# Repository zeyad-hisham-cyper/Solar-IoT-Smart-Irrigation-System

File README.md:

# 🌱 Solar-Powered IoT Smart Irrigation System

A distributed, low-power irrigation platform that closes the loop between soil sensors in the
field and a phone in your hand. It is built from **three cooperating subsystems**:

1. **Zone firmware** (ESP32) — battery/solar sensor + valve endpoints that measure soil
   moisture, temperature and water flow, and open/close a solenoid valve on command.
2. **Gateway firmware** (ESP32) — the single Internet-connected node. It runs the irrigation
   decision engine, drives the pump, enforces safety, talks to the zones over **ESP-NOW**, and
   mirrors all state to the cloud over Wi-Fi.
3. **Flutter mobile app** — a real-time dashboard that monitors every zone and lets the user
   switch modes and control valves/pump, talking only to **Firebase Realtime Database**.

> This document is the single engineering reference for the entire project — hardware,
> firmware, cloud schema and mobile app. It is detailed enough for a new engineer to
> understand the architecture, build/flash/run every component, debug issues, and extend the
> system without additional documentation.

---

## Team

Graduation project — **Electronics and Communications Department**, Faculty of Engineering
Sciences and Arts, **Misr International University (MIU)**, Cairo, 2026.

| Member |
|--------|
| Zeyad Hisham |
| Abdelrahman Adel |
| Amr Yasser |
| Ahmed Mohamed Saad |

**Supervisor:** Dr. Ibrahiem Abdalla

---

## Table of Contents

- [1. System Architecture](#1-system-architecture)
- [2. Repository Layout](#2-repository-layout)
- [3. Hardware Reference](#3-hardware-reference)
  - [3.1 Boards & Power](#31-boards--power)
  - [3.2 Complete GPIO Mapping](#32-complete-gpio-mapping)
  - [3.3 Bill of Materials (minimum)](#33-bill-of-materials-minimum)
  - [3.4 PCB Design (KiCad)](#34-pcb-design-kicad)
- [4. ESP-NOW Network](#4-esp-now-network)
- [5. Firmware Design](#5-firmware-design)
  - [5.1 Software Architecture](#51-software-architecture)
  - [5.2 Gateway (Control) Node](#52-gateway-control-node)
  - [5.3 Zone Node](#53-zone-node)
  - [5.4 Communication Flow](#54-communication-flow)
  - [5.5 Packet Structures](#55-packet-structures)
  - [5.6 State Machines](#56-state-machines)
  - [5.7 Sensor Processing](#57-sensor-processing)
  - [5.8 Irrigation Decision Logic](#58-irrigation-decision-logic)
  - [5.9 Power Management](#59-power-management)
  - [5.10 Status LEDs & Buzzer](#510-status-leds--buzzer)
- [6. Cloud — Firebase](#6-cloud--firebase)
  - [6.1 Architecture](#61-architecture)
  - [6.2 Database Schema](#62-database-schema)
- [7. Mobile App (Flutter)](#7-mobile-app-flutter)
  - [7.1 Architecture](#71-architecture)
  - [7.2 Project Structure](#72-project-structure)
  - [7.3 Command & Control Mapping](#73-command--control-mapping)
- [8. Build, Flash & Run](#8-build-flash--run)
- [9. Configuration Guide](#9-configuration-guide)
- [10. Testing Procedures](#10-testing-procedures)
- [11. Troubleshooting](#11-troubleshooting)
- [12. Error Handling & Safety](#12-error-handling--safety)
- [13. Future Improvements](#13-future-improvements)
- [14. License](#14-license)

---

## 1. System Architecture

The system is organised into four layers. Zone nodes never touch the Internet; the gateway is
the only cloud-connected device; the app talks only to Firebase.

```mermaid
flowchart TD
    subgraph ZL["Zone Layer (battery / solar)"]
        Z1["Zone Node 1<br/>soil • temp • flow • valve"]
        Z2["Zone Node N<br/>soil • temp • flow • valve"]
    end
    subgraph CL["Control Layer (gateway)"]
        G["Gateway / Control Node<br/>irrigation engine • pump • water level"]
    end
    subgraph CLD["Cloud Layer"]
        FB[("Firebase RTDB")]
        WAPI(("OpenWeather API"))
    end
    subgraph AL["Application Layer"]
        APP["Flutter Dashboard"]
    end

    Z1 <-- "ESP-NOW (2.4 GHz)" --> G
    Z2 <-- "ESP-NOW (2.4 GHz)" --> G
    G <-- "Wi-Fi / HTTPS" --> FB
    G -- "HTTPS GET" --> WAPI
    APP <-- "RTDB SDK" --> FB
```

| Direction | Path | Protocol |
|-----------|------|----------|
| Zone → Gateway | soil moisture, temperature, flow, needs-water | ESP-NOW |
| Gateway → Zone | valve open/close commands | ESP-NOW (reliable, ACK'd) |
| Gateway → Firebase | gateway state, zone telemetry, weather | HTTPS REST (PUT) |
| Firebase → Gateway | mode, per-zone config, manual commands | HTTPS REST (GET poll, 2 s) |
| Firebase ↔ App | all reads + command writes | Firebase SDK (real-time streams) |

**The Flutter app never communicates with the ESP32 boards directly** — all interaction is
mediated through Firebase Realtime Database.

### Design objectives

| Objective | How it is met |
|-----------|---------------|
| Reliable irrigation | Closed-loop moisture control + duration limits + weather awareness |
| Safety | Pump active-LOW safe-OFF, valve 10-min auto-close, dry-run protection, uncalibrated-reading rejection, ACK'd valve commands |
| Maintainability | Pure-C component-based HAL/Services separation; layered Flutter app; documented APIs |
| Scalability | Up to 8 zones per gateway (NVS registry); extensible, versioned ESP-NOW protocol |
| Low power | Soil-sensor power-gating, event-driven tasks, no busy-wait polling |
| Observability | Per-board status LEDs + buzzer driven by an explicit lifecycle state machine |

---

## 2. Repository Layout

```
.
├── README.md                      # ← this document (the single project reference)
├── docs/
│   └── architecture.png           # system architecture diagram
│
├── PCBs/                          # KiCad hardware design (gateway + zone boards)
│   ├── Control Schematic.png      # rendered gateway schematic
│   ├── control 3D.png             # gateway board 3D render
│   ├── Zone Schematic.png         # rendered zone schematic
│   ├── Zone 3D.png                # zone board 3D render
│   ├── control/                   # GATEWAY KiCad project (.kicad_sch/_pcb/_pro) + BoM csv
│   ├── Zone/                      # ZONE KiCad project + gerbers/ + final_gerber/ + lib/
│   ├── light/                     # SMART LIGHTING relay board KiCad project + BoM csv
│   ├── gerbers/                   # fabrication outputs (control, zones, light)
│   ├── fritzing/                  # early breadboard prototypes (.fzz) + wiring images
│   └── BOM/                       # proof-of-concept bill of materials (.xlsx)
│
├── firebase/                      # Firebase RTDB data model (db.md), seed data, sample export
│
├── firmware/                      # ESP-IDF firmware (two apps + shared components)
│   ├── db.json                    # authoritative Firebase RTDB schema export
│   ├── common/                    # shared components (EXTRA_COMPONENT_DIRS)
│   │   ├── esp_now/               # protocol + reliable send
│   │   ├── led_driver/            # non-blocking LED (blink/pulse) via esp_timer
│   │   ├── buzzer_driver/         # active/passive buzzer pattern player
│   │   └── state_machine/         # tiny reusable FSM engine
│   ├── control/                   # GATEWAY app
│   │   └── main/
│   │       ├── HAL/{Pump,WaterLevel,WiFi,DcMotor,FlowMeter}/
│   │       ├── Services/{FirebaseAuth,FirebaseDB,FirebaseSync,Weather,IrrigationEngine}/
│   │       └── include/{app_config.h, firebase_config.h}
│   └── zone/                      # ZONE app
│       └── main/
│           ├── HAL/{soil_moisture,ds18b20,valve,FlowMeter}/
│           └── include/app_config.h
│
└── app/                           # Flutter mobile dashboard
    ├── lib/
    │   ├── core/                  # constants, theme, utils
    │   ├── data/                  # repositories + Firebase services
    │   ├── models/                # data models (gateway, zone, command, weather)
    │   ├── providers/             # Riverpod providers (streams + commands)
    │   ├── presentation/          # screens + widgets
    │   └── routes/                # GoRouter configuration
    ├── android/ ios/ web/ windows/ macos/ linux/
    └── pubspec.yaml
```

Design rules (firmware): hardware access lives in `HAL/`; business logic in `Services/`;
cross-cutting board-agnostic drivers live in `common/`. The irrigation engine never touches
GPIO directly — it calls the pump driver and sends ESP-NOW commands.

---

## 3. Hardware Reference

### 3.1 Boards & Power

Two ESP32-WROOM-32 board types share a solar power architecture
(solar → MPPT → battery → buck/LDO rails).

```mermaid
flowchart LR
    SOLAR["Solar Panel 12-24V"] --> MPPT["MPPT Charger"]
    MPPT --> BAT["Battery 12V"]
    BAT --> VBAT["VBAT rail<br/>pump, valves"]
    BAT --> BUCK["Buck 5V"] --> V5["5V rail<br/>flow meter, driver logic"]
    BUCK --> LDO["LDO 3.3V"] --> V3["3.3V rail<br/>ESP32, sensors"]
```

| Board | Qty | Actuators | Sensors | Indicators |
|-------|-----|-----------|---------|------------|
| **Gateway / Control** | 1 | Pump (MOSFET, active-LOW) | Water level (ADC) | Green/Yellow/Red LED + buzzer |
| **Zone** | N (≤8) | Solenoid valve (MOSFET) | Soil moisture (ADC, power-gated), DS18B20 temp, YFS-401 flow | Green/Yellow/Red LED + buzzer |

| Rail | Voltage | Consumers |
|------|---------|-----------|
| VBAT | 12–24 V | Water pump motor, solenoid valves |
| 5 V | 5 V | Flow meter, motor-driver logic |
| 3.3 V | 3.3 V | ESP32, DS18B20, soil moisture sensor, all GPIO logic |

**Power budget (typical):** ESP32 Wi-Fi 80–160 mA · ESP32 ESP-NOW 50–100 mA · soil sensor
10–20 mA (power-gated) · DS18B20 <1.5 mA · YFS-401 5–10 mA · solenoid coil 200–400 mA ·
pump 1–5 A (load dependent).

**Key PCB notes:** keep a 10 mm clear zone under the ESP32 PCB antenna; place a 4.7 kΩ
DS18B20 pull-up near its connector; route ADC traces away from switching/motor lines; add a
flyback diode across the solenoid coil and freewheeling diodes on the motor driver outputs;
100 nF close to each VCC pin + 10 µF bulk per rail.

### 3.2 Complete GPIO Mapping

**Gateway / Control Board**

| Function | GPIO | Notes |
|----------|------|-------|
| Pump switch | **GPIO25** | MOSFET, **active-LOW**: LOW = ON, HIGH = OFF (safe). Pull-up holds OFF at boot |
| Water level sensor | GPIO34 | ADC1_CH6, input-only |
| Buzzer | GPIO32 | LEDC tone (passive) |
| Green LED | GPIO26 | Healthy / idle |
| Yellow LED | GPIO27 | Busy / pump running |
| Red LED | GPIO14 | Fault / dry tank |

**Zone Board**

| Function | GPIO | Notes |
|----------|------|-------|
| Soil moisture ADC | GPIO35 | ADC1_CH7, input-only, power-gated |
| Soil sensor VCC control | GPIO25 | HIGH = sensor powered |
| Calibration button | GPIO0 | Boot button, active-LOW, ISR |
| DS18B20 data | GPIO18 | 1-Wire, 4.7 kΩ pull-up |
| Flow sensor (YFS-401) | GPIO19 | Rising-edge ISR |
| Valve | GPIO23 | MOSFET, HIGH = open |
| Red LED | GPIO32 | Fault / not paired |
| Yellow LED | GPIO26 | Valve open / calibrating |
| Green LED | GPIO27 | Paired / idle |
| Buzzer | GPIO33 | LEDC tone (passive) |

All pin assignments are centralised in each app's `main/include/app_config.h`.

### 3.3 Bill of Materials (minimum)

**Zone node:** ESP32-WROOM-32 · AMS1117-3.3 LDO · MP1584/LM2596 buck · IRLZ44N N-MOSFET
(valve) · 1N4007 flyback · 4.7 kΩ (DS18B20 pull-up) · 330 Ω (MOSFET gate) · 10 kΩ (flow
pull-up) · capacitive soil sensor · DS18B20 · YFS-401 flow meter · 12 V solenoid valve ·
tactile switches (calibration + reset) · screw terminals.

**Gateway node:** ESP32-WROOM-32 · motor driver (MOSFET/H-bridge) · AMS1117-3.3 LDO ·
Schottky freewheeling diodes · bypass/bulk caps · reset switch · screw terminals (pump,
water-level sensor, power).

### 3.4 PCB Design (KiCad)

The gateway and zone boards are custom two-layer PCBs designed in **KiCad 8**; a third board
drives the campus **smart-lighting** relays. The full design sources live in
[`PCBs/`](PCBs/) — schematics, layouts, fabrication gerbers and the bill-of-materials CSVs are
all version-controlled, so each board can be reviewed, edited and re-fabricated from this repo.

| Board | KiCad project | Fabrication outputs | BoM |
|-------|---------------|---------------------|-----|
| **Gateway / Control** | [`PCBs/control/control.kicad_pro`](PCBs/control/control.kicad_pro) | — | [`control.csv`](PCBs/control/control.csv) |
| **Zone** | [`PCBs/Zone/Zone.kicad_pro`](PCBs/Zone/Zone.kicad_pro) | [`gerber/`](PCBs/Zone/gerber/), [`final_gerber/`](PCBs/Zone/final_gerber/) | [`Zone.csv`](PCBs/Zone/Zone.csv) |
| **Smart Lighting** | [`PCBs/light/light.kicad_pro`](PCBs/light/light.kicad_pro) | [`gerbers/light/`](PCBs/gerbers/light/) | [`light.csv`](PCBs/light/light.csv) |

Fabrication-ready gerber + drill sets for every board are also collected in
[`PCBs/gerbers/`](PCBs/gerbers/) (`control/`, `zones/`, `Zones Single/`, `light/`). Early
breadboard prototypes made in **Fritzing** (`.fzz` + wiring images) are in
[`PCBs/fritzing/`](PCBs/fritzing/), and the proof-of-concept bill of materials is in
[`PCBs/BOM/`](PCBs/BOM/).

#### Smart Lighting board

A 12 V relay controller for campus lighting, built around a **NodeMCU (ESP-12E)**:

| Block | Parts |
|-------|-------|
| MCU | NodeMCU 1.0 (ESP-12E) on two 15-pin headers |
| Power | 12 V input → **LM2596** buck module → 5 V / 3.3 V rails, bulk + decoupling capacitors |
| Load switching | 4 × **SRD-12VDC-SL-C** relays, each isolated by a **PC817** optocoupler and driven by a **2N2222** transistor with a **1N4007** flyback diode (hierarchical sheet [`realy_module.kicad_sch`](PCBs/light/realy_module.kicad_sch)) |
| Indicators | 2 × **74HC595** shift registers driving 16 status LEDs |
| I/O | 5 × 2-pin screw terminals for supply and lamp outputs, TL2285EE push-button |

The zone project bundles its custom symbol/footprint library and the third-party YAAJ **LM2596**
buck-converter footprint under [`PCBs/Zone/lib/`](PCBs/Zone/lib/). Open a board with
`File → Open Project` in KiCad and use the 3D viewer to inspect placement and clearances.

| Gateway schematic | Gateway 3D | Zone schematic | Zone 3D |
|:-----------------:|:----------:|:--------------:|:-------:|
|  |  |  |  |

> **Repo hygiene:** KiCad auto-backups (`*-backups/`), autosaves, the `fp-info-cache`, per-user
> `*.kicad_prl` state and the heavy vendor 3D models (`*.step`/`*.wrl`) are git-ignored. The
> LM2596 STEP/WRL previews are downloadable from the vendor if you want the full 3D render.

---

## 4. ESP-NOW Network

A star topology: one gateway, up to 8 zones. No router is required for the local link; the
gateway additionally joins the home Wi-Fi AP for cloud access.

```mermaid
flowchart TD
    G(("Gateway<br/>sender_id = 0"))
    Z1["Zone 1"]
    Z2["Zone 2"]
    Zn["Zone N (<=8)"]
    G <-->|"DISCOVERY / ASSIGN / COMMAND"| Z1
    G <-->|"ZONE_DATA"| Z1
    G <--> Z2
    G <--> Zn
```

- **Protocol version 4** (`ESP_NOW_PROTOCOL_VERSION`). Every packet starts with a 3-byte
  header `{version, msg_type, sender_id}`; mismatched versions are dropped.
- **Channel:** the gateway tracks its Wi-Fi AP channel and pins ESP-NOW to it. Zones scan
  channels 1–13 during discovery, then persist the pairing.
- **MAC obfuscation:** zone MACs are XOR-obfuscated (key `0xA5`) inside discovery payloads — a
  lightweight anti-sniffing deterrent, not encryption.
- **Reliable delivery:** safety-critical valve commands use `EspNow_SendReliable()`, which
  waits for the link-layer ACK and retransmits (up to 4 attempts). Telemetry is best-effort.
- **Recovery:** a zone that sees 5 consecutive send failures wipes its pairing and re-discovers.

---

## 5. Firmware Design

ESP-IDF **v5.x**, component-based, **two apps + shared components**, pure C throughout.
Shared components are discovered through `EXTRA_COMPONENT_DIRS=../common` in each project's
top-level `CMakeLists.txt`.

### 5.1 Software Architecture

```
firmware/
├── common/        esp_now · led_driver · buzzer_driver · state_machine   (shared)
├── control/       GATEWAY  →  HAL/ + Services/ + include/
└── zone/          ZONE     →  HAL/ + include/
```

### 5.2 Gateway (Control) Node

```mermaid
flowchart TD
    RX["ESP-NOW RX cb"] -->|ZONE_DATA| ENG["Irrigation Engine<br/>(mutex-protected)"]
    RX -->|DISCOVERY_RESP| REG["Zone Registry (NVS)"]
    WL["Water-level task (5 s)"] --> ENG
    WEA["Weather task (3 h)"] --> ENG
    POLL["Firebase poll (2 s)"] --> ENG
    CYC["Irrigation cycle (1 s)"] --> ENG
    ENG -->|valve cmd, reliable| TX["ESP-NOW TX"]
    ENG --> PUMP["Pump (GPIO25, active-LOW)"]
    ENG --> UP["Firebase upload (2 s)"]
    ENG --> FSM["Lifecycle FSM -> LEDs/Buzzer"]
```

Responsibilities: zone discovery/registration (NVS), telemetry ingestion, the irrigation
decision engine, pump control with dry-run protection, weather fetch, and Firebase sync.

### 5.3 Zone Node

```mermaid
flowchart TD
    SL["Sensor loop (3 s)<br/>soil • temp • flow"] --> SNAP["Shared snapshot<br/>(spinlock)"]
    SNAP --> TX["TX task (2 s)<br/>ZONE_DATA"]
    RX["ESP-NOW RX cb"] -->|COMMAND| VALVE["Valve (GPIO23)"]
    RX -->|DISCOVERY/ASSIGN| PAIR["Pairing (NVS)"]
    BTN["Calibration button ISR"] --> CAL["Calibration task"]
    SAFE["Valve safety task (5 s)"] --> VALVE
    FSM["Lifecycle FSM -> LEDs/Buzzer"]
```

Responsibilities: sensor acquisition, pairing/discovery, valve actuation on gateway command,
interrupt-driven calibration, and the valve safety timeout (10-min auto-close).

### 5.4 Communication Flow

**Discovery & assignment**

```mermaid
sequenceDiagram
    participant G as Gateway
    participant Z as Zone
    G-->>Z: DISCOVERY_REQ (broadcast, periodic)
    Z-->>G: DISCOVERY_RESP (obfuscated MAC)
    G->>G: find/register zone in NVS -> zone_id
    G-->>Z: ZONE_ASSIGN (zone_id)  [unicast]
    Z->>Z: persist {zone_id, gateway MAC} in NVS
```

**Steady-state telemetry & control**

```mermaid
sequenceDiagram
    participant Z as Zone
    participant G as Gateway
    loop every 2 s
        Z-->>G: ZONE_DATA (sm, temp, flow, vol, needs_water)
    end
    Note over G: engine decides per cycle (1 s)
    G-->>Z: COMMAND open/close (reliable, ACK + retry)
    Z->>Z: drive valve, FSM -> IRRIGATING / PAIRED_IDLE
```

### 5.5 Packet Structures

All structs are `__attribute__((packed))` and prefixed with the common header.

```c
typedef struct __attribute__((packed)) {
    uint8_t version;     // = ESP_NOW_PROTOCOL_VERSION (4)
    uint8_t msg_type;    // EspNow_MsgType_t
    uint8_t sender_id;   // zone id, or 0 for the gateway
} EspNow_MessageHeader_t;
```

| Type | ID | Direction | Payload (beyond header) |
|------|----|-----------|-------------------------|
| `ZONE_DATA` | 1 | Zone → GW | `moisture%` (0xFF = invalid), `temp_x10` (-999 = invalid), `needs_water`, `total_volume_ml`, `flow_rate_x100` |
| `COMMAND` | 2 | GW → Zone | `target_zone_id`, `open_valve` |
| `DISCOVERY_REQ` | 3 | GW → bcast | — |
| `DISCOVERY_RESP` | 4 | Zone → GW | `obfuscated_mac[6]` |
| `ZONE_ASSIGN` | 5 | GW → Zone | `assigned_zone_id` |

Sentinels: `ESP_NOW_MOISTURE_INVALID = 0xFF`, `ESP_NOW_TEMP_INVALID = -999`. The gateway treats
an invalid moisture as out-of-range and will never irrigate on it.

### 5.6 State Machines

Both apps drive an explicit lifecycle FSM (`common/state_machine`) whose transitions are logged
and mapped to the status indicators.

**Gateway**

```mermaid
stateDiagram-v2
    [*] --> BOOT
    BOOT --> INIT
    INIT --> INIT_ESPNOW
    INIT_ESPNOW --> CONNECT_WIFI
    CONNECT_WIFI --> RUNNING
    RUNNING --> IRRIGATING: pump on
    IRRIGATING --> RUNNING: pump off
    RUNNING --> TANK_DRY: level < threshold
    TANK_DRY --> RUNNING: refilled
    INIT_ESPNOW --> ERROR: ESP-NOW init fail
```

**Zone**

```mermaid
stateDiagram-v2
    [*] --> BOOT
    BOOT --> INIT
    INIT --> DISCOVERY
    DISCOVERY --> PAIRED_IDLE: ZONE_ASSIGN
    PAIRED_IDLE --> IRRIGATING: COMMAND open
    IRRIGATING --> PAIRED_IDLE: COMMAND close / safety timeout
    PAIRED_IDLE --> CALIBRATING: button
    CALIBRATING --> PAIRED_IDLE
    DISCOVERY --> ERROR: pairing failed -> restart
```

### 5.7 Sensor Processing

| Sensor | Processing | Failure handling |
|--------|-----------|------------------|
| **Soil moisture** | Power-gate ON → 100 ms settle → 64-sample average → map with NVS dry/wet calibration → 0–100 % → power OFF | **Uncalibrated/invalid ⇒ `valid=false`**; the zone transmits `0xFF` so the gateway never irrigates on it |
| **DS18B20** | 12-bit conversion, up to 3 retries; ~750 ms conv time | Invalid ⇒ `temp_x10 = -999`; does not block irrigation |
| **YFS-401 flow** | Rising-edge ISR increments a cumulative counter; rate from Δpulses/Δt; volume recomputed from the cumulative count in 64-bit (no truncation loss); spinlock guards counters across cores | Zero on first call; safe against div-by-zero |
| **Water level** | 16–32 sample average mapped between calibrated empty/full raw values; either polarity | Read failure ⇒ keep last value; `valid=false` disables dry-run gating (fails open) |

### 5.8 Irrigation Decision Logic

The engine runs every second under a mutex. Order of operations each cycle:

```mermaid
flowchart TD
    A["heartbeat check<br/>(mark stale zones inactive)"] --> B["duration check<br/>(close expired valves)"]
    B --> C{"water available?"}
    C -- no --> D["stop all + pump OFF<br/>state = TANK_DRY"]
    C -- yes --> E{mode}
    E -- AUTO --> F["per zone: if rain -> stop;<br/>else sm<th -> open (until sm>=th);<br/>sm>=th -> close"]
    E -- MANUAL --> G["pump=false -> stop all;<br/>per zone: v=true -> open (with dur);<br/>v=false -> close"]
    F --> H["pump OFF if no active zone"]
    G --> H
```

**Safety invariants**
- Pump ON requires water available **and** at least one eligible zone below threshold.
- A zone is *eligible* only if its data is valid, fresh (< 10 s) and in range — an invalid
  (`0xFF`) moisture is rejected at ingestion and can never start irrigation.
- The pump turns ON before any valve opens (`PUMP_SETTLE_DELAY_MS`), and OFF once no valve is open.
- Manual mode still enforces the threshold and dry-run safety.

### 5.9 Power Management

This deployment uses an **always-on** model because the gateway commands zone valves in real
time and auto mode is closed-loop on the live moisture stream. Within that model:

- **Soil sensor is power-gated** — energised only for the ~100 ms measurement window.
- **No busy-wait polling.** Calibration is interrupt-driven (button ISR); flow counting is
  ISR-driven; tasks block on timers/notifications/event-groups rather than spinning.
- **Water level** is sampled at a slow cadence (5 s).
- **Outputs default to safe/off** at boot and are disabled before the system goes idle.

> **Deep sleep was deliberately not enabled.** A sleeping zone cannot receive live valve
> `COMMAND` packets, and auto mode holds a valve open until the *streamed* moisture crosses the
> threshold. Adopting deep sleep requires a **zone-autonomous duty-cycle** protocol redesign
> (wake → measure → report → receive a fixed duration → run the valve locally → sleep), listed
> under [Future Improvements](#13-future-improvements).

### 5.10 Status LEDs & Buzzer

**Gateway**

| State | Green | Yellow | Red | Buzzer |
|-------|:-----:|:------:|:---:|--------|
| BOOT / INIT | off | fast blink | off | — |
| CONNECT_WIFI | off | slow blink | off | — |
| RUNNING (idle) | **on** | off | off | success chirp on entry |
| IRRIGATING | off | **on** | off | — |
| TANK_DRY | off | off | blink | warning |
| ERROR | off | off | **on** | error pattern |

**Zone**

| State | Green | Yellow | Red | Buzzer |
|-------|:-----:|:------:|:---:|--------|
| BOOT / INIT | off | fast blink | off | — |
| DISCOVERY (unpaired) | off | off | slow blink | — |
| PAIRED_IDLE | **on** | off | off | success on pairing |
| IRRIGATING (valve open) | off | **on** | off | — |
| CALIBRATING | off | fast blink | off | success/error on finish |
| ERROR | off | off | **on** | error pattern |

Buzzer patterns: `success` (rising two-tone), `warning` (two beeps), `error` (three low beeps),
`alarm` (continuous until stopped).

---

## 6. Cloud — Firebase

### 6.1 Architecture

```mermaid
sequenceDiagram
    participant G as Gateway
    participant ID as Identity Toolkit
    participant DB as RTDB
    G->>ID: signInWithPassword(email, pw)
    ID-->>G: idToken
    loop every 2 s
        G->>DB: PUT gateways/g1, zones/zX  (?auth=idToken)
        G->>DB: GET gateways/g1.mode, zones/zX.{th,dur}, commands/g1
    end
    Note over G,DB: On HTTP 401 -> re-auth -> retry once
```

- **Auth:** email/password → `idToken`, attached as `?auth=` to every REST call. A `401`
  triggers a transparent re-login and one retry.
- **Upload (2 s, or immediate on critical change):** `gateways/g1` and `zones/z1..z2`.
- **Poll (2 s):** gateway `mode`, per-zone `th`/`dur`, and `commands/g1`.
- **Resilience:** read failures preserve the last known config; uploads never block the engine.
  Timestamps are only published once SNTP has synced (no bogus `-1`).

### 6.2 Database Schema

Authoritative export: [`firmware/db.json`](firmware/db.json). Firmware field names match exactly.

```
gateways/g1/
  ├─ mode        (string)  "auto" | "manual"        [cloud -> device]
  ├─ pump        (bool)    pump running              [device -> cloud]
  ├─ waterLevel  (number)  reservoir 0-100 %         [device -> cloud]
  └─ lastSeen    (number)  epoch ms                  [device -> cloud]

zones/z{1,2}/
  ├─ g    (string)  parent gateway id "g1"
  ├─ sm   (number)  soil moisture 0-100 %
  ├─ t    (number)  temperature C
  ├─ f    (number)  flow rate L/min
  ├─ v    (bool)    valve open
  ├─ lu   (number)  last update epoch ms
  ├─ th   (number)  moisture threshold %  [cloud -> device]
  ├─ dur  (number)  irrigation duration s [cloud -> device]
  └─ history/{id}   time-series readings (temp, moisture, flow, water used, valve, ts)

commands/g1/
  ├─ pump (bool)            master pump enable (false = stop all)  [cloud -> device]
  ├─ ts   (number)          command timestamp
  └─ z/z{1,2}/{ v(bool), d(number seconds), commandId, status }    [cloud -> device]

commandAcks/g1/z{1,2}/  { commandId, status, executedAt, message } [device -> cloud]

weather/  { temperature, humidity, condition, timestamp }          [device -> cloud]
```

**Schema notes**
- `f` carries the instantaneous flow rate in L/min (consistent with its name).
- `commands/g1/pump` is honoured as a master kill in manual mode.
- `waterLevel` is a real reading from the gateway's ADC.
- `history/` and `commandAcks/` support the app's charts and command-acknowledgement UX.

---

## 7. Mobile App (Flutter)

A cross-platform Flutter dashboard for real-time monitoring and manual control. It reads and
writes Firebase Realtime Database only — the same project the gateway authenticates against.

### 7.1 Architecture

Layered architecture with **Riverpod** for state and **GoRouter** for navigation. Firebase
listeners produce streams that Riverpod `StreamProvider`s expose to the UI; user actions go
through repositories that write command paths.

```
Firebase RTDB
   │  onValue streams
   ▼
Repositories (gateway / zone / command / weather / history)
   │
   ▼
Riverpod providers  →  Screens & widgets  →  user action  →  Repository.write(...)  →  RTDB
```

| Concern | Choice |
|---------|--------|
| Framework / language | Flutter 3.x · Dart 3.x |
| State management | `flutter_riverpod` (stream-native, compile-safe) |
| Routing | `go_router` |
| Backend | `firebase_core`, `firebase_database`, `firebase_auth` |
| UI | `google_fonts`, `percent_indicator`, `shimmer`, `connectivity_plus`, `intl` |

The app is **dark-themed, portrait-locked**, and enables Firebase offline persistence (10 MB
cache) so the last-known state is shown without connectivity.

### 7.2 Project Structure

```
app/lib/
├── main.dart                       # entry: Firebase init, persistence, ProviderScope
├── firebase_options.dart           # generated by FlutterFire CLI
├── core/
│   ├── constants/                  # firebase_paths.dart, app_constants.dart
│   ├── theme/                      # app_theme.dart, app_colors.dart
│   └── utils/                      # timestamp_utils.dart
├── data/
│   └── repositories/               # gateway, zone, command, weather, history
├── models/                         # gateway, zone_data, zone_reading, zone_command, weather, app_enums
├── providers/                      # gateway, zone, weather, command, history, alerts, connectivity
├── presentation/
│   ├── screens/                    # main, dashboard, config, alerts, zone_detail
│   └── widgets/                    # zone_card, moisture_gauge, weather_widget, mode_toggle,
│                                   #   valve_control_button, pump_status_badge, glass_card, …
└── routes/
    └── app_router.dart             # GoRouter: '/' (MainScreen) + '/zone/:zoneId'
```

**Navigation:** a single `MainScreen` hosts a bottom navigation bar — **Dashboard**, **Config**
and **Alerts** — plus a `/zone/:zoneId` detail route. Screens:

| Screen | Purpose |
|--------|---------|
| **Dashboard** | Gateway online/mode/pump status, weather widget, per-zone summary cards |
| **Zone Detail** | Moisture gauge, temperature, flow, valve state, threshold/duration editors, history chart |
| **Config** | System mode toggle (auto/manual) and per-zone thresholds & durations |
| **Alerts** | Gateway-offline, stale-zone and connectivity warnings |

**Staleness rules:** zone stale > 15 s (amber badge), zone offline > 60 s (red, controls
disabled), gateway offline > 30 s (banner). Manual valve/pump controls are enabled only in
manual mode and require a confirmation dialog.

### 7.3 Command & Control Mapping

The gateway polls `commands/g1` every 2 s; the app writes these paths and the firmware acts on
the next poll (≈0–2 s latency). Path constants live in `lib/core/constants/firebase_paths.dart`.

| User action | Write | Path | Value |
|-------------|-------|------|-------|
| Switch mode | `set` | `gateways/g1/mode` | `"auto"` / `"manual"` |
| Open zone valve | `update` | `commands/g1/z/<id>` | `{ v: true, d: <seconds> }` |
| Close zone valve | `update` | `commands/g1/z/<id>` | `{ v: false, d: 0 }` |
| Pump on/off | `set` | `commands/g1/pump` | `true` / `false` |
| Set threshold | `set` | `zones/<id>/th` | `0–100` |
| Set duration | `set` | `zones/<id>/dur` | seconds |
| (every command) | `set` | `commands/g1/ts` | epoch |

---

## 8. Build, Flash & Run

### Firmware (ESP-IDF v5.x)

Prerequisites: ESP-IDF v5.x installed and exported (`. $IDF_PATH/export.sh`), target `esp32`.

```bash
# Gateway / control board
cd firmware/control
cp main/include/secrets.example.h main/include/secrets.h   # first time only: add your credentials
idf.py set-target esp32
idf.py build
idf.py -p <PORT> flash monitor       # PORT e.g. COM5 (Windows) or /dev/ttyUSB0 (Linux)

# Zone board (separate terminal / build dir)
cd firmware/zone
idf.py set-target esp32
idf.py build
idf.py -p <PORT> flash monitor
```

The zone app pulls `espressif/ds18b20` and `espressif/onewire_bus` via the component manager
(`zone/main/idf_component.yml`).

**First-boot sequence**
1. Flash the **gateway** first; confirm it connects to Wi-Fi and logs its channel.
2. Flash a **zone**; it scans channels, pairs, and persists its `zone_id`.
3. To re-pair a zone, erase its NVS: `idf.py -p <PORT> erase-flash`, then re-flash.

### Mobile app (Flutter)

Prerequisites: Flutter SDK 3.x (stable), an Android/iOS toolchain, and access to the Firebase
project.

```bash
cd app
flutter pub get

# (first time) regenerate Firebase config for your project:
#   dart pub global activate flutterfire_cli
#   flutterfire configure
flutter run
```

`google-services.json` / `GoogleService-Info.plist` are placed by the FlutterFire CLI and are
**git-ignored** — each developer configures their own.

---

## 9. Configuration Guide

| What | Where |
|------|-------|
| Wi-Fi SSID / password | `firmware/control/main/include/secrets.h` → `WIFI_SSID`, `WIFI_PASS` |
| OpenWeather API key | `secrets.h` → `WEATHER_API_KEY` |
| Pump pin / polarity | `control/.../app_config.h` → `PUMP_RELAY_GPIO`, `PUMP_ACTIVE_HIGH` |
| Water-level calibration | `WATER_LEVEL_RAW_EMPTY/FULL`, `WATER_LEVEL_DRY_THRESHOLD` |
| Status LED / buzzer pins | both `app_config.h` files |
| Default thresholds & durations | `DEFAULT_Z*_THRESHOLD`, `DEFAULT_Z*_DURATION` (overridable from Firebase) |
| Firebase API key / login / DB URL | `secrets.h` → `FIREBASE_API_KEY`, `FIREBASE_AUTH_EMAIL`, `FIREBASE_AUTH_PASSWORD`, `FIREBASE_DB_URL` |
| Firebase IDs & timing | `firmware/control/main/include/firebase_config.h` |
| ESP-NOW channel (zone hint) | `firmware/zone/main/include/app_config.h` → `ESP_NOW_CHANNEL` |
| App Firebase config | `app/lib/firebase_options.dart` (generated) |
| App RTDB paths & zone IDs | `app/lib/core/constants/firebase_paths.dart` |

> **Secrets:** all credentials live in `firmware/control/main/include/secrets.h`, which is
> git-ignored. Before building the gateway, copy the template and fill in your own values:
>
> ```bash
> cp firmware/control/main/include/secrets.example.h firmware/control/main/include/secrets.h
> ```
>
> The build stops with a clear `#error` if `secrets.h` is missing. The `.gitignore` also excludes
> `*.env`, `google-services.json` and `GoogleService-Info.plist`.

---

## 10. Testing Procedures

| Test | Procedure | Expected |
|------|-----------|----------|
| Pairing | Power gateway, then zone | Zone LED: red-blink → green; gateway logs `ZONE_ASSIGN` |
| Calibration | Press zone button; follow wet/dry prompts | Yellow fast-blink during; success chirp; subsequent `sm` valid |
| Uncalibrated safety | Erase zone NVS, run without calibrating | Gateway logs moisture INVALID; **no irrigation** |
| Auto irrigation | Set `mode=auto`, dry the sensor below `th` | Pump ON, valve opens, stops when `sm ≥ th` |
| Manual control | `mode=manual`, set `commands/g1/z/z1/{v:true,d:30}` | Valve opens ~30 s; `v:false` closes immediately |
| Dry-run protection | Drop water level below threshold | `TANK_DRY`, pump inhibited, red blink + warning |
| Valve reliability | Power-cycle a zone mid-cycle | Gateway logs reliable-send retries; valve reaches commanded state |
| Comms loss | Power off gateway while a valve is open | Zone auto-closes valve at 10-min safety timeout |
| App round-trip | Toggle mode / open a valve in the app | Firebase path updates; gateway acts within ~2 s; UI reflects new state |

---

## 11. Troubleshooting

| Symptom | Likely cause | Fix |
|---------|--------------|-----|
| Zone never pairs | Channel mismatch / out of range | Confirm gateway Wi-Fi channel; bring nodes closer; check zone `DISCOVERY` logs |
| Moisture always INVALID | Sensor never calibrated | Run the calibration routine (button) |
| Pump never runs | Tank dry, or all zones above threshold | Check `waterLevel`, thresholds, sensor validity |
| Pump runs at boot | Wrong polarity wiring | Verify `PUMP_ACTIVE_HIGH=false` and MOSFET is low-side active-LOW |
| No cloud updates | Wi-Fi / auth failure | Check SSID/pass, Firebase key/URL, look for `401` → re-auth logs |
| Valve stuck open | Lost comms | Zone safety closes at 10 min; check ESP-NOW link |
| `waterLevel` looks wrong | Uncalibrated ADC references | Set `WATER_LEVEL_RAW_EMPTY/FULL` for your sensor |
| App shows stale data | Gateway offline or no internet | Check gateway power/Wi-Fi; the app banner indicates connectivity state |

---

## 12. Error Handling & Safety

- **Fail-safe defaults:** pump and valve initialise OFF/closed with pull resistors holding the
  safe level through reset; outputs are driven safe before idle.
- **Input validation:** every ESP-NOW packet is length- and version-checked; sensor ranges are
  validated; invalid moisture cannot trigger irrigation.
- **Acknowledged commands:** valve commands retransmit until ACK'd (bounded) so a dropped frame
  doesn't strand a valve until the safety timeout.
- **Graceful cloud degradation:** read failures keep the last known config; uploads retry next
  cycle; `401` re-authenticates and retries once.
- **Self-recovery:** zones wipe pairing and re-discover after repeated send failures; the
  gateway enters the ERROR state on ESP-NOW init failure.
- **Watchdog-friendly:** no unbounded busy loops; long operations yield via FreeRTOS delays.
- **Concurrency:** engine state is mutex-protected; zone sensor snapshots and the flow counter
  use spinlocks for consistent, cross-core-safe access.

---

## 13. Future Improvements

1. **Zone-autonomous deep sleep** protocol (§5.9) for multi-month battery life.
2. **Encrypted ESP-NOW** (LMK/PMK) replacing MAC obfuscation.
3. **Per-zone water budgeting** using the accurate flow totals (leak detection, litres/day).
4. **OTA updates** for both firmware apps (partition table already supports it).
5. **Firebase `PATCH`** instead of `PUT` to avoid clobbering concurrent edits; exponential backoff.
6. **Sequence numbers / dedup** in ESP-NOW for stricter idempotency.
7. **Scale beyond 2 cloud zones** — extend the gateway's Firebase mapping to the full 8-zone registry.
8. **Push notifications** (FCM) for alerts; **historical analytics** dashboard in the app.
9. **Move secrets to NVS / secure storage** out of source control.

---

## 14. License

Released under the **MIT License**. See [`LICENSE`](LICENSE).

---

*Graduation Project — Solar-Powered IoT Smart Irrigation System.*
*Firmware: `firmware/control` (gateway), `firmware/zone` (zone), `firmware/common` (shared).*
*Cloud schema: `firmware/db.json`. Mobile app: `app/`.*

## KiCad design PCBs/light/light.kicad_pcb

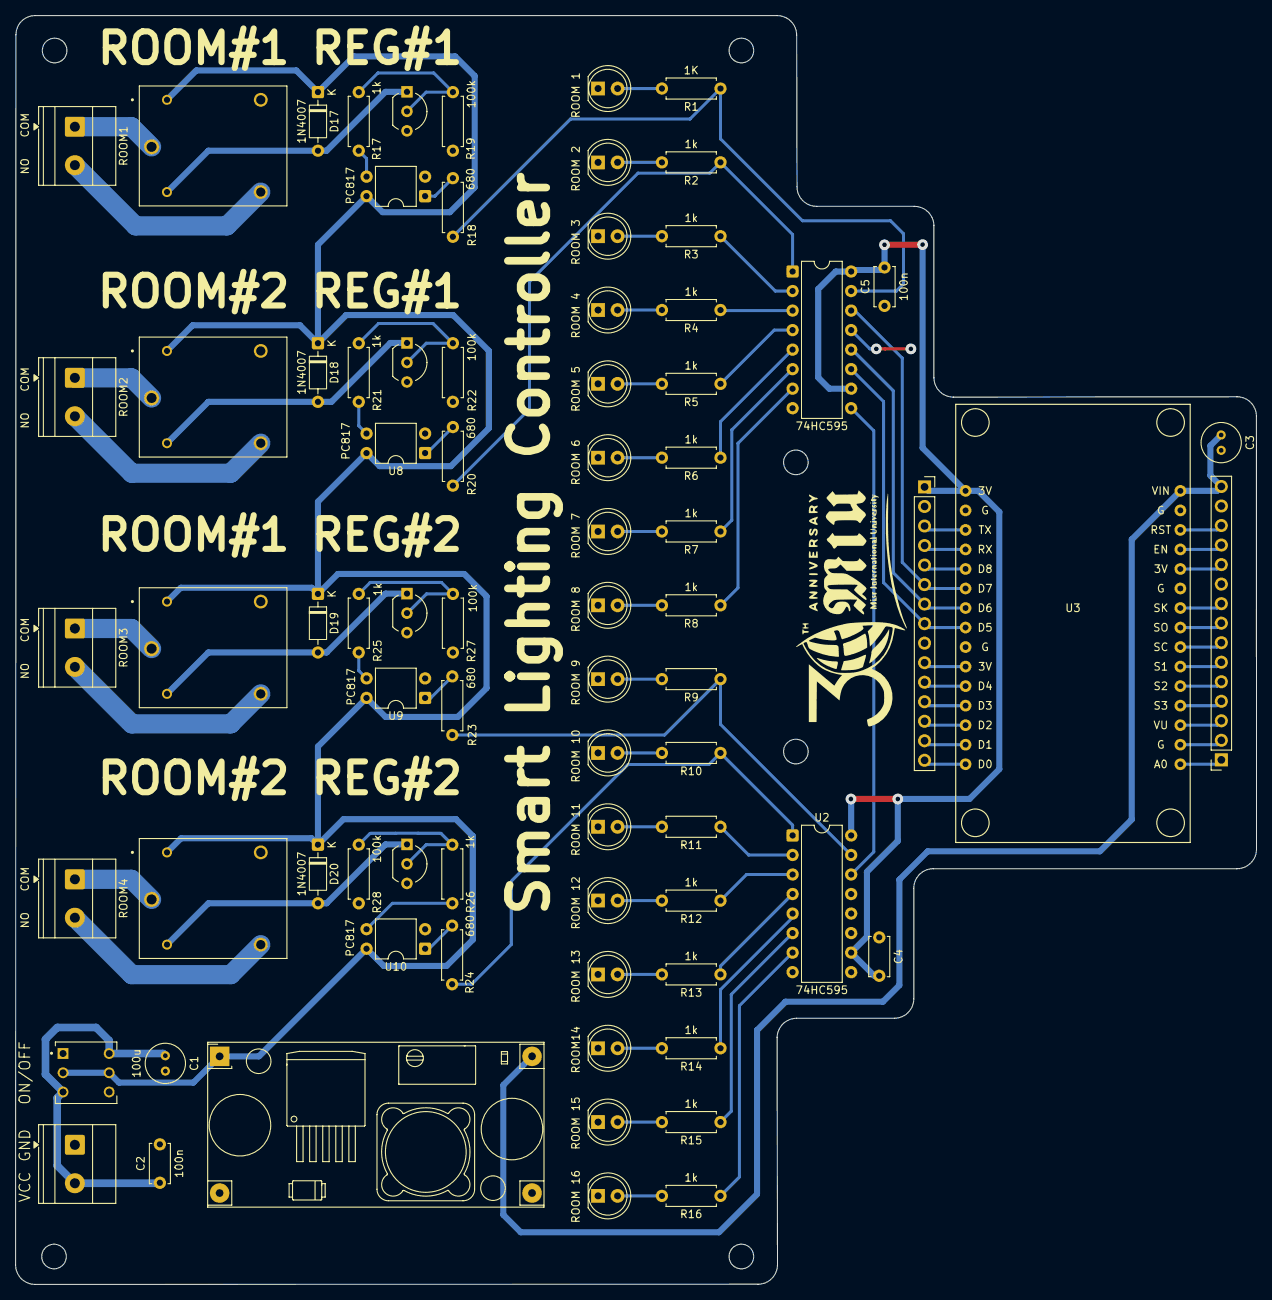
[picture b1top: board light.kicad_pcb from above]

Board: 2 copper layers, 161.4 x 165.0 mm, 77 parts (0 on the bottom side), 86 nets.

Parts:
C1: 100u; C_Radial_D5.0mm_H5.0mm_P2.00mm
C2, C4, C5: 100n; C_Disc_D5.0mm_W2.5mm_P5.00mm
C3: 470u; C_Radial_D5.0mm_H5.0mm_P2.00mm
D17, D18, D19, D20: 1N4007; D_DO-35_SOD27_P7.62mm_Horizontal
J5, J6: Conn_01x15_Pin; PinSocket_1x15_P2.54mm_Vertical
J8: Screw_Terminal_01x02; TerminalBlock_Phoenix_MKDS-1,5-2_1x02_P5.00mm_Horizontal
K1, K2, K3, K4: SRD-12VDC-SL-C; RELAY_SRD-12VDC-SL-C
ON/OFF: TL2285EE; SW_TL2285EE
Q1, Q2, Q3, Q4: 2n2222; TO-92_Inline_Wide
R1: 1K; R_Axial_DIN0207_L6.3mm_D2.5mm_P7.62mm_Horizontal
R2, R3, R4, R5, R6, R7, R8, R9, R10, R11, R12, R13, R14, R15, R16, R17, R21, R25, R26: 1k; R_Axial_DIN0207_L6.3mm_D2.5mm_P7.62mm_Horizontal
R18, R20, R23, R24: 680; R_Axial_DIN0207_L6.3mm_D2.5mm_P7.62mm_Horizontal
R19, R22, R27, R28: 100k; R_Axial_DIN0207_L6.3mm_D2.5mm_P7.62mm_Horizontal
ROOM1, ROOM2, ROOM3, ROOM4: Screw_Terminal_01x02; TerminalBlock_Phoenix_MKDS-1,5-2_1x02_P5.00mm_Horizontal
ROOM14: LED; LED_D5.0mm
ROOM 1, ROOM 2, ROOM 3, ROOM 4, ROOM 5, ROOM 6, ROOM 7, ROOM 8, ROOM 9, ROOM 10, ROOM 11, ROOM 12, ROOM 13, ROOM 15, ROOM 16: LED; LED_D5.0mm
U1, U2: 74HC595; DIP-16_W7.62mm
U3: NodeMCU1.0(ESP-12E); NodeMCU-LoLinV3
U4: YAAJ_DCDC_StepDown_LM2596
U5, U8, U9, U10: PC817; DIP-4_W7.62mm

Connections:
5V: C3.1, J5.15, U3.15 (VIN), U4.4 (Vout)
+3.3V: C4.2, C5.2, J6.1, U1.10 (~SRCLR), U1.16 (VCC), U2.10 (~SRCLR), U2.16 (VCC), U3.16 (3.3V)
+12V: D17.1 (K), D18.1 (K), D19.1 (K), D20.1 (K), K1.COIL1, K2.COIL1, K3.COIL1, K4.COIL1, ON/OFF.2, ON/OFF.5, U4.1 (Vin), U5.4, U8.4, U9.4, U10.4
+12V_IN: C1.1, C2.1, J8.2, ON/OFF.3, ON/OFF.4
/relay_module/COM1: K1.COM, ROOM1.1
/relay_module/COM2: K2.COM, ROOM2.1
/relay_module/COM3: K3.COM, ROOM3.1
/relay_module/COM4: K4.COM, ROOM4.1
/relay_module/NO1: K1.NO, ROOM1.2
/relay_module/NO2: K2.NO, ROOM2.2
/relay_module/NO3: K3.NO, ROOM3.2
/relay_module/NO4: K4.NO, ROOM4.2
CLOCK: J6.8, U1.11 (SRCLK), U3.23 (D5(GPIO14))
DATA: J6.6, U1.14 (SER), U3.21 (D7(GPIO13))
GND: C1.2, C2.2, C3.2, C4.1, C5.1, J5.10, J5.14, J6.2, J6.9, J8.1, Q1.3 (E), Q2.3 (E), Q3.3 (E), Q4.3 (E), R19.1, R22.1, R27.1, R28.1, ROOM14.1 (K), ROOM 1.1 (K), ROOM 2.1 (K), ROOM 3.1 (K), ROOM 4.1 (K), ROOM 5.1 (K), ROOM 6.1 (K), ROOM 7.1 (K), ROOM 8.1 (K), ROOM 9.1 (K), ROOM 10.1 (K), ROOM 11.1 (K), ROOM 12.1 (K), ROOM 13.1 (K), ROOM 15.1 (K), ROOM 16.1 (K), U1.8 (GND), U1.13 (~OE), U2.8 (GND), U2.13 (~OE), U3.10 (GND), U3.14 (GND), U3.17 (GND), U3.24 (GND), U4.2 (GND), U4.3 (GND), U5.2, U8.2, U9.2, U10.2
LATCH: J6.7, U1.12 (RCLK), U3.22 (D6(GPIO12))
unnamed: R1.2, ROOM 1.2 (A)
unnamed: R2.2, ROOM 2.2 (A)
unnamed: R3.2, ROOM 3.2 (A)
unnamed: R4.2, ROOM 4.2 (A)
unnamed: R5.2, ROOM 5.2 (A)
unnamed: R6.2, ROOM 6.2 (A)
unnamed: R7.2, ROOM 7.2 (A)
unnamed: R8.2, ROOM 8.2 (A)
unnamed: R9.2, ROOM 9.2 (A)
unnamed: R10.2, ROOM 10.2 (A)
unnamed: R11.2, ROOM 11.2 (A)
unnamed: R12.2, ROOM 12.2 (A)
unnamed: R13.2, ROOM 13.2 (A)
unnamed: R14.2, ROOM14.2 (A)
unnamed: R15.2, ROOM 15.2 (A)
unnamed: R16.2, ROOM 16.2 (A)
unnamed: D17.2 (A), K1.COIL2, Q1.1 (C)
unnamed: D18.2 (A), K2.COIL2, Q2.1 (C)
unnamed: D19.2 (A), K3.COIL2, Q3.1 (C)
unnamed: D20.2 (A), K4.COIL2, Q4.1 (C)
unnamed: J5.1, U3.1 (A0(ADC0))
unnamed: J5.2, U3.2 (RSV)
unnamed: J5.3, U3.3 (RSV)
unnamed: J5.4, U3.4 (SD3(GPIO10))
unnamed: J5.5, U3.5 (SD2(GPIO9))
unnamed: J5.6, U3.6 (SD1(MOSI))
unnamed: J5.7, U3.7 (CMD(CS))
unnamed: J5.8, U3.8 (SDO(MISO))
unnamed: J5.9, U3.9 (CLK(SCLK))
unnamed: J5.11, U3.11 (3.3V)
unnamed: J5.12, U3.12 (EN)
unnamed: J5.13, U3.13 (RST)
unnamed: J6.3, U3.18 (TX(GPIO1))
unnamed: J6.4, U3.19 (RX(DPIO3))
unnamed: J6.5, U3.20 (D8(GPIO15))
unnamed: J6.10, U3.25 (3.3V)
unnamed: J6.11, U3.26 (D4(GPIO2))
unnamed: J6.12, U3.27 (D3(GPIO0))
unnamed: J6.13, U3.28 (D2(GPIO4))
unnamed: J6.14, U3.29 (D1(GPIO5))
unnamed: J6.15, U3.30 (D0(GPIO16))
unnamed: Q1.2 (B), R17.2, R19.2
unnamed: Q2.2 (B), R21.2, R22.2
unnamed: Q3.2 (B), R25.2, R27.2
unnamed: Q4.2 (B), R26.2, R28.2
unnamed: R17.1, U5.3
unnamed: R18.2, U5.1
unnamed: R20.2, U8.1
unnamed: R21.1, U8.3
unnamed: R23.2, U9.1
unnamed: R24.2, U10.1
unnamed: R25.1, U9.3
unnamed: R26.1, U10.3
unnamed: U1.9 (QH'), U2.14 (SER)
OUT1: R1.1, R18.1, U1.15 (QA)
OUT2: R2.1, R20.1, U1.1 (QB)
OUT3: R3.1, U1.2 (QC)
OUT4: R4.1, U1.3 (QD)
OUT5: R5.1, U1.4 (QE)
OUT6: R6.1, U1.5 (QF)
OUT7: R7.1, U1.6 (QG)
OUT8: R8.1, U1.7 (QH)
OUT9: R9.1, R23.1, U2.15 (QA)
OUT10: R10.1, R24.1, U2.1 (QB)
OUT11: R11.1, U2.2 (QC)
OUT12: R12.1, U2.3 (QD)
OUT13: R13.1, U2.4 (QE)
OUT14: R14.1, U2.5 (QF)
OUT15: R15.1, U2.6 (QG)
OUT16: R16.1, U2.7 (QH)

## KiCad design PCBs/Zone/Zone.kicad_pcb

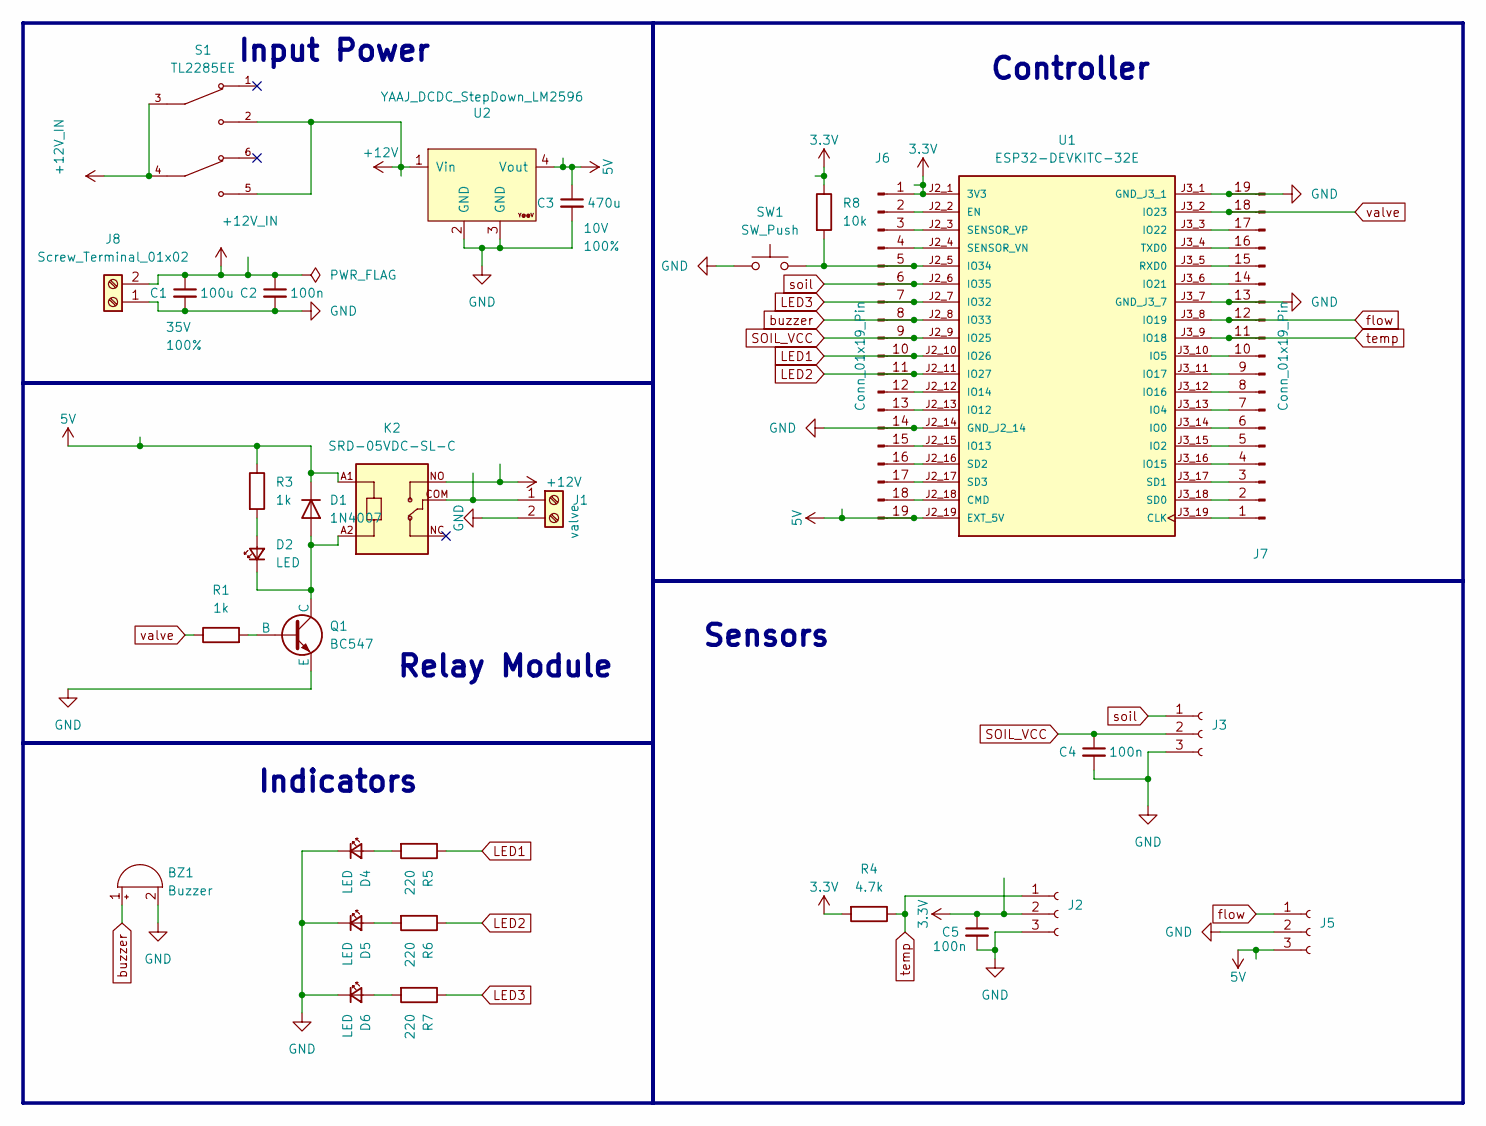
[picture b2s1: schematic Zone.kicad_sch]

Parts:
BZ1: Buzzer; Buzzer_12x9.5RM7.6
C1: 100u; C_Radial_D5.0mm_H5.0mm_P2.00mm; Voltage 35V; Tolerance 100%
C2, C4, C5: 100n; C_Disc_D5.0mm_W2.5mm_P5.00mm; Voltage 35V; Tolerance 100%
C3: 470u; C_Radial_D5.0mm_H5.0mm_P2.00mm; Voltage 10V; Tolerance 100%
D1: 1N4007; D_DO-35_SOD27_P7.62mm_Horizontal
D2, D4, D5, D6: LED; LED_D5.0mm
J1, J8: Screw_Terminal_01x02; TerminalBlock_Phoenix_MKDS-1,5-2_1x02_P5.00mm_Horizontal
J2, J3, J5: Conn_01x03_Socket; JST_XH_B3B-XH-A_1x03_P2.50mm_Vertical
J6, J7: Conn_01x19_Pin; PinSocket_1x19_P2.54mm_Vertical
K2: SRD-05VDC-SL-C; RELAY_SRD-05VDC-SL-C
Q1: BC547; TO-92_Inline_Wide
R1, R3: 1k; R_Axial_DIN0207_L6.3mm_D2.5mm_P7.62mm_Horizontal
R4: 4.7k; R_Axial_DIN0207_L6.3mm_D2.5mm_P7.62mm_Horizontal
R5, R6, R7: 220; R_Axial_DIN0207_L6.3mm_D2.5mm_P7.62mm_Horizontal
R8: 10k; R_Axial_DIN0207_L6.3mm_D2.5mm_P7.62mm_Horizontal
S1: TL2285EE; SW_TL2285EE; PARTREV B
SW1: SW_Push; SW_PUSH_6mm
U1: ESP32-DEVKITC-32E; MODULE_ESP32-DEVKITC-32E; PARTREV 1.4
U2: YAAJ_DCDC_StepDown_LM2596

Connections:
3.3V: C5.1, J2.2, J6.1, R4.2, R8.1, U1.J2_1 (3V3)
5V: C3.1, D1.1 (K), J5.3, J6.19, K2.A1, R3.1, U1.J2_19 (EXT_5V), U2.4 (Vout)
+12V: K2.NO, S1.2, S1.5, U2.1 (Vin)
+12V_IN: C1.1, C2.1, J8.2, S1.3, S1.4
GND: BZ1.2 (-), C1.2, C2.2, C3.2, C4.2, C5.2, D4.1 (K), D5.1 (K), D6.1 (K), J1.2, J2.3, J3.3, J5.2, J6.14, J7.13, J7.19, J8.1, Q1.3 (E), SW1.1, U1.J2_14 (GND_J2_14), U1.J3_1 (GND_J3_1), U1.J3_7 (GND_J3_7), U2.2 (GND), U2.3 (GND)
LED1: J6.10, R5.1, U1.J2_10 (IO26)
LED2: J6.11, R6.1, U1.J2_11 (IO27)
LED3: J6.7, R7.1, U1.J2_7 (IO32)
unnamed: D1.2 (A), D2.1 (K), K2.A2, Q1.1 (C)
unnamed: D2.2 (A), R3.2
unnamed: D4.2 (A), R5.2
unnamed: D5.2 (A), R6.2
unnamed: D6.2 (A), R7.2
unnamed: J1.1, K2.COM
unnamed: J6.2, U1.J2_2 (EN)
unnamed: J6.3, U1.J2_3 (SENSOR_VP)
unnamed: J6.4, U1.J2_4 (SENSOR_VN)
unnamed: J6.5, R8.2, SW1.2, U1.J2_5 (IO34)
unnamed: J6.12, U1.J2_12 (IO14)
unnamed: J6.13, U1.J2_13 (IO12)
unnamed: J6.15, U1.J2_15 (IO13)
unnamed: J6.16, U1.J2_16 (SD2)
unnamed: J6.17, U1.J2_17 (SD3)
unnamed: J6.18, U1.J2_18 (CMD)
unnamed: J7.1, U1.J3_19 (CLK)
unnamed: J7.2, U1.J3_18 (SD0)
unnamed: J7.3, U1.J3_17 (SD1)
unnamed: J7.4, U1.J3_16 (IO15)
unnamed: J7.5, U1.J3_15 (IO2)
unnamed: J7.6, U1.J3_14 (IO0)
unnamed: J7.7, U1.J3_13 (IO4)
unnamed: J7.8, U1.J3_12 (IO16)
unnamed: J7.9, U1.J3_11 (IO17)
unnamed: J7.10, U1.J3_10 (IO5)
unnamed: J7.14, U1.J3_6 (IO21)
unnamed: J7.15, U1.J3_5 (RXD0)
unnamed: J7.16, U1.J3_4 (TXD0)
unnamed: J7.17, U1.J3_3 (IO22)
unnamed: Q1.2 (B), R1.2
SOIL_VCC: C4.1, J3.2, J6.9, U1.J2_9 (IO25)
buzzer: BZ1.1 (+), J6.8, U1.J2_8 (IO33)
flow: J5.1, J7.12, U1.J3_8 (IO19)
soil: J3.1, J6.6, U1.J2_6 (IO35)
temp: J2.1, J7.11, R4.1, U1.J3_9 (IO18)
valve: J7.18, R1.1, U1.J3_2 (IO23)

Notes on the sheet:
Controller
Relay Module
Input Power
Indicators
Sensors

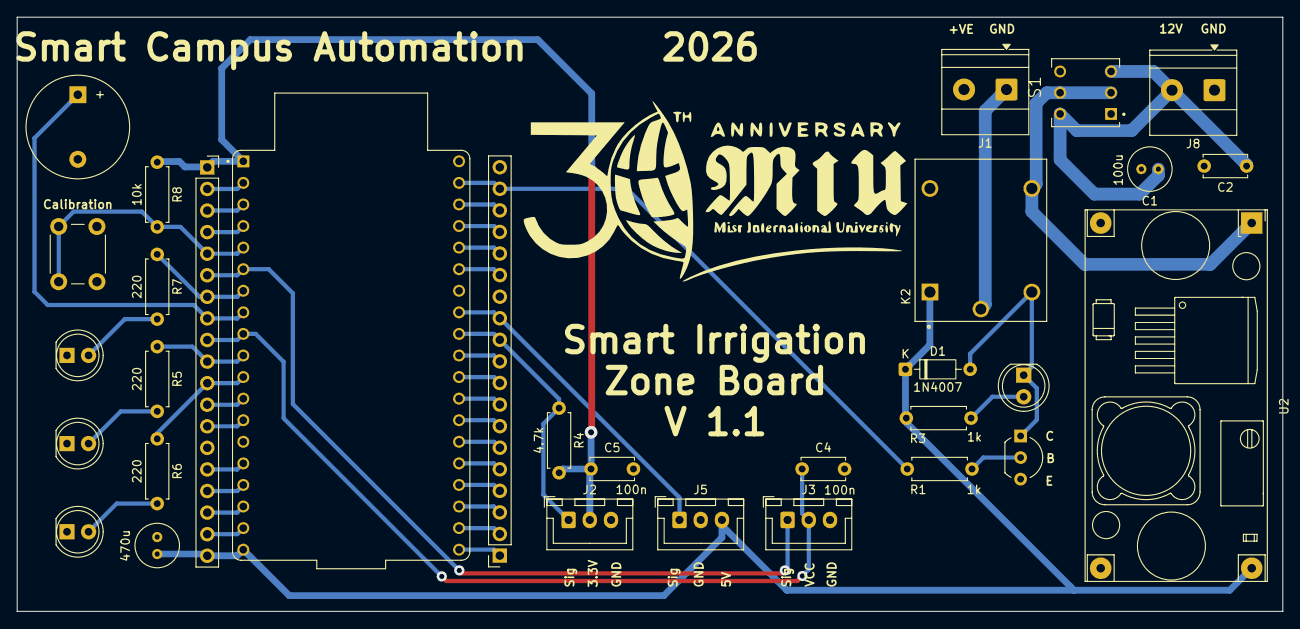
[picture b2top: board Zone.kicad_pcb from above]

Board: 2 copper layers, 149.0 x 70.0 mm, 31 parts (0 on the bottom side), 45 nets.

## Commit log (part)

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2026-01-27 Adding Soil Moisture Driver
2026-01-31 Updating SMS Driver
2026-02-01 refine the sms sensor and add ds18b20 dependecies
2026-02-01 adding ds18b20 wrapper driver
2026-03-01 Adding esp-now
2026-03-07 Drafting Cloud Lambda and add some addition drivers
2026-04-10 Connecting the gateway to cloud
2026-04-16 updating the topolgy
2026-06-24 Final Expo Commit
2026-06-24 adding pcbs

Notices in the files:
README.md:
License: MIT
